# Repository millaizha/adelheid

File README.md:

# 𝕬𝖉𝖊𝖑𝖍𝖊𝖎𝖉

The Adelheid is a 75% Alice-like keyboard.  
It's a fork of FateNozomi's Arisu files: [Arisu PCB](https://github.com/FateNozomi/arisu-pcb) &amp; [Arisu case](https://github.com/FateNozomi/arisu-case)

This repo is a hand-wired version forked from [floookay's Adelheid](https://github.com/floookay/adelheid) with some changes.

This repository includes files for:

- a layered case &rarr; [README.md](./case/README.md)

## Changes in this fork

Here is a list of things I added in this fork in comparison to the original Adelheid:

- [x] replaced page up with a rotary encoder
- [x] lowered home, end, and page up keys (will change into media keys)
- [x] added win and right control keys
- [x] used pro micro as the controller
- [x] changed thickness of some acrylics

## Layout

A spaced 75% layout on top of the Alice/Arisu-layout.

[Keyboard-Layout-Editor](http://www.keyboard-layout-editor.com/#/gists/3d5f924367b3b31ac1beb2d660264759)

## Firmware

See [firmware](https://github.com/millaizha/adelheid-hand-wire/tree/master/firmware)

## Images

For more images see [images.md](./IMAGES.md).

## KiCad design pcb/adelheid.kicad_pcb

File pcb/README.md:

# 𝕬𝖉𝖊𝖑𝖍𝖊𝖎𝖉 - PCB

**Disclaimer:** This PCB revision uses a pin for backlight support that is not PWM enabled. This causes the LEDs to flicker. Everything else works without a problem.  
You can fix this yourself by following [these instructions](../REVISION-UPGRADE-INSTRUCTIONS.md).

The PCB for the Adelheid was designed using KiCAD on top of the Arisu PCB files.

## Changes compared to the Arisu PCB

- [x] Added a spaced function row
- [x] Added footprint for stepped caps lock key
- [x] Changed the micro USB port to a tht mini USB port
- [x] Added single color underglow and key lighting *(underglow on it's own works fine. Both combined have **not been tested yet**)*

## FateNozomi's Arisu description

>アリス PCB designed using KiCad. The layout is inspired by Lyn's EM7 and TGR Alice with some modification of my own.
>
> Key differences:
>
> - I removed the extra [B] key on the right half and shifted the [NM,.?] row > to the left by 0.25U.
> - Shifted the 3 keys to the right and added arrow keys.
> - Tweaked the bottom so that the 1.5U keys doesn't protrude out a little.
>
> Shifting the [NM,.?] row to the left by 0.25U required quite some work on the arrangement of keys for the right half.  
> As a result, this does not give the same typing experience as Lyn's EM7 and TGR Alice.
> Lyn's EM7 and TGR Alice uses the home row as the center point to vertically align both halves while I used the number row instead.  
> Due to the nature of staggered keyboards, aligning using the number row resulted in the home row not being aligned.

The Adelheid inherits these changes from the Arisu.

## KiCAD libraries in use

- [ai03/MX_Only](https://github.com/ai03-2725/MX_Alps_Hybrid/tree/master/MX_Only.pretty) for MX switch footprints (local copy in `./lib/`)
- [Keebio-Parts](https://github.com/keebio/Keebio-Parts.pretty) for mini USB port footprint

## Parts list

### SMD

All SMD parts are listed in the [BOM](./adelheid.gerber/adelheid.csv) with their corresponding value, label and LCSC number.  
If you opt in for LED backlighting/underglow please make sure to use the correct resistor size for your LEDs in order for your PCB to function correctly. See [here](#backlighting) for led resistor estimations.

### THT

- 82x MX switches
- 1x through-hole mini USB 2.0 port (MX-54819-0519)
- (optional) 82x 3mm single color LEDs

## Backlighting

To calculate what resistors you'll need you can use my [backlight calculator spreadsheet](./backlight.ods) to calculate the estimated total power draw. Enter your LED specifications and either enter the desired current per LED or enter the resistor size which you are planning on using. The spreadsheet should calculate the total power draw and compare it to the allowed power draw of USB 2.0 (500 mA). *I'm no electrical engineer so please be cautious.*

<!--  -->

## **Disclaimer**

Use these files at your own risk.  
*Note:* Lighting features have not been entirely tested yet! Please be cautious.

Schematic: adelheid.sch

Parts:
C1, C2: 22pF; C_0805_HandSoldering
C3: 10uF; C_0805_HandSoldering
C4: 1uF (±10%); C_0805_HandSoldering
C5: 1uF; C_0805_HandSoldering
C6, C7, C8, C9: 0.1uF; C_0805_HandSoldering
H1, H2, H3, H4, H5, H6, H7, H8: MountingHole; MountingHole_2.2mm_M2_Pad
J1: USB_B_Mini; USB-Mini-B_2leg
J2: MISO; Pin_Header_Straight_1x01_Pitch2.54mm
J3, J12: VCC; Pin_Header_Straight_1x01_Pitch2.54mm
J4: SCK; Pin_Header_Straight_1x01_Pitch2.54mm
J5: MOSI; Pin_Header_Straight_1x01_Pitch2.54mm
J6: RES; Pin_Header_Straight_1x01_Pitch2.54mm
J7, J15: GND; Pin_Header_Straight_1x01_Pitch2.54mm
J8: PF4; Pin_Header_Straight_1x01_Pitch2.54mm
J9: PF5; Pin_Header_Straight_1x01_Pitch2.54mm
J13: D+; Pin_Header_Straight_1x01_Pitch2.54mm
J14: D-; Pin_Header_Straight_1x01_Pitch2.54mm
Q1: 2N7002; SOT-23
R1, R2: 22; R_0805_2012Metric_Pad1.15x1.40mm_HandSolder
R3, R4: 10K; R_0805_2012Metric_Pad1.15x1.40mm_HandSolder
R5: 1.5K; R_0805_2012Metric_Pad1.15x1.40mm_HandSolder
SWR1: SW_Push; SW_SPST_TL3342
U1: USBLC6-2SC6; SOT-23-6_Handsoldering
U2: ATmega32U4-AU; TQFP-44_10x10mm_Pitch0.8mm
Y1: Crystal_GND24; Crystal_SMD_SeikoEpson_FA238-4pin_3.2x2.5mm_HandSoldering

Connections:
/MISO: J2.1, U2.11 (PB3); also elsewhere on the board
/MOSI: J5.1, U2.10 (PB2)
/PF4: J8.1, U2.39 (PF4)
/PF5: J9.1, U2.38 (PF5)
/SCK: J4.1, U2.9 (PB1); also elsewhere on the board
/col0: U2.41 (PF0); also elsewhere on the board
/col1: U2.40 (PF1); also elsewhere on the board
/col2: U2.1 (PE6); also elsewhere on the board
/col3: U2.32 (PC7); also elsewhere on the board
/col4: U2.31 (PC6); also elsewhere on the board
/col5: U2.30 (PB6); also elsewhere on the board
/col6: U2.25 (PD4); also elsewhere on the board
/col8: U2.8 (PB0); also elsewhere on the board
/col9: U2.12 (PB7); also elsewhere on the board
/col10: U2.29 (PB5); also elsewhere on the board
/col11: U2.28 (PB4); also elsewhere on the board
/col12: U2.27 (PD7); also elsewhere on the board
/col13: U2.26 (PD6); also elsewhere on the board
/ledGND: Q1.3; also elsewhere on the board
/row0: U2.18 (PD0); also elsewhere on the board
/row1: U2.19 (PD1); also elsewhere on the board
/row2: U2.20 (PD2); also elsewhere on the board
/row3: U2.21 (PD3); also elsewhere on the board
/row4: U2.22 (PD5); also elsewhere on the board
/row5: U2.36 (PF7); also elsewhere on the board
/~RES~: J6.1, R3.2, SWR1.2, U2.13 (~RESET)
D+: R1.1, U2.4 (D+)
D-: R2.1, U2.3 (D-)
GND: C1.1, C2.2, C3.2, C4.2, C5.2, C6.2, C7.2, C8.2, C9.2, J1.5 (GND), J1.6 (Shield), J7.1, J15.1, Q1.2, R4.2, SWR1.1, U1.2 (GND), U2.5 (UGND), U2.15 (GND), U2.23 (GND), U2.35 (GND), U2.43 (GND), Y1.2, Y1.4
unnamed: C4.1, U2.6 (UCAP)
unnamed: J1.2 (D-), J14.1, R2.2, U1.4 (IO2)
unnamed: J1.3 (D+), J13.1, R1.2, U1.6 (IO1)
unnamed: Q1.1, R5.2
unnamed: R4.1, U2.33 (~HWB~/PE2)
unnamed: R5.1, U2.37 (PF6)
VCC: C3.1, C5.1, C6.1, C7.1, C8.1, C9.1, J1.1 (VBUS), J3.1, J12.1, R3.1, U1.5 (VBUS), U2.2 (UVCC), U2.7 (VBUS), U2.14 (VCC), U2.24 (AVCC), U2.34 (VCC), U2.44 (AVCC); also elsewhere on the board
XTAL1: C1.2, U2.17 (XTAL1), Y1.1
XTAL2: C2.1, U2.16 (XTAL2), Y1.3

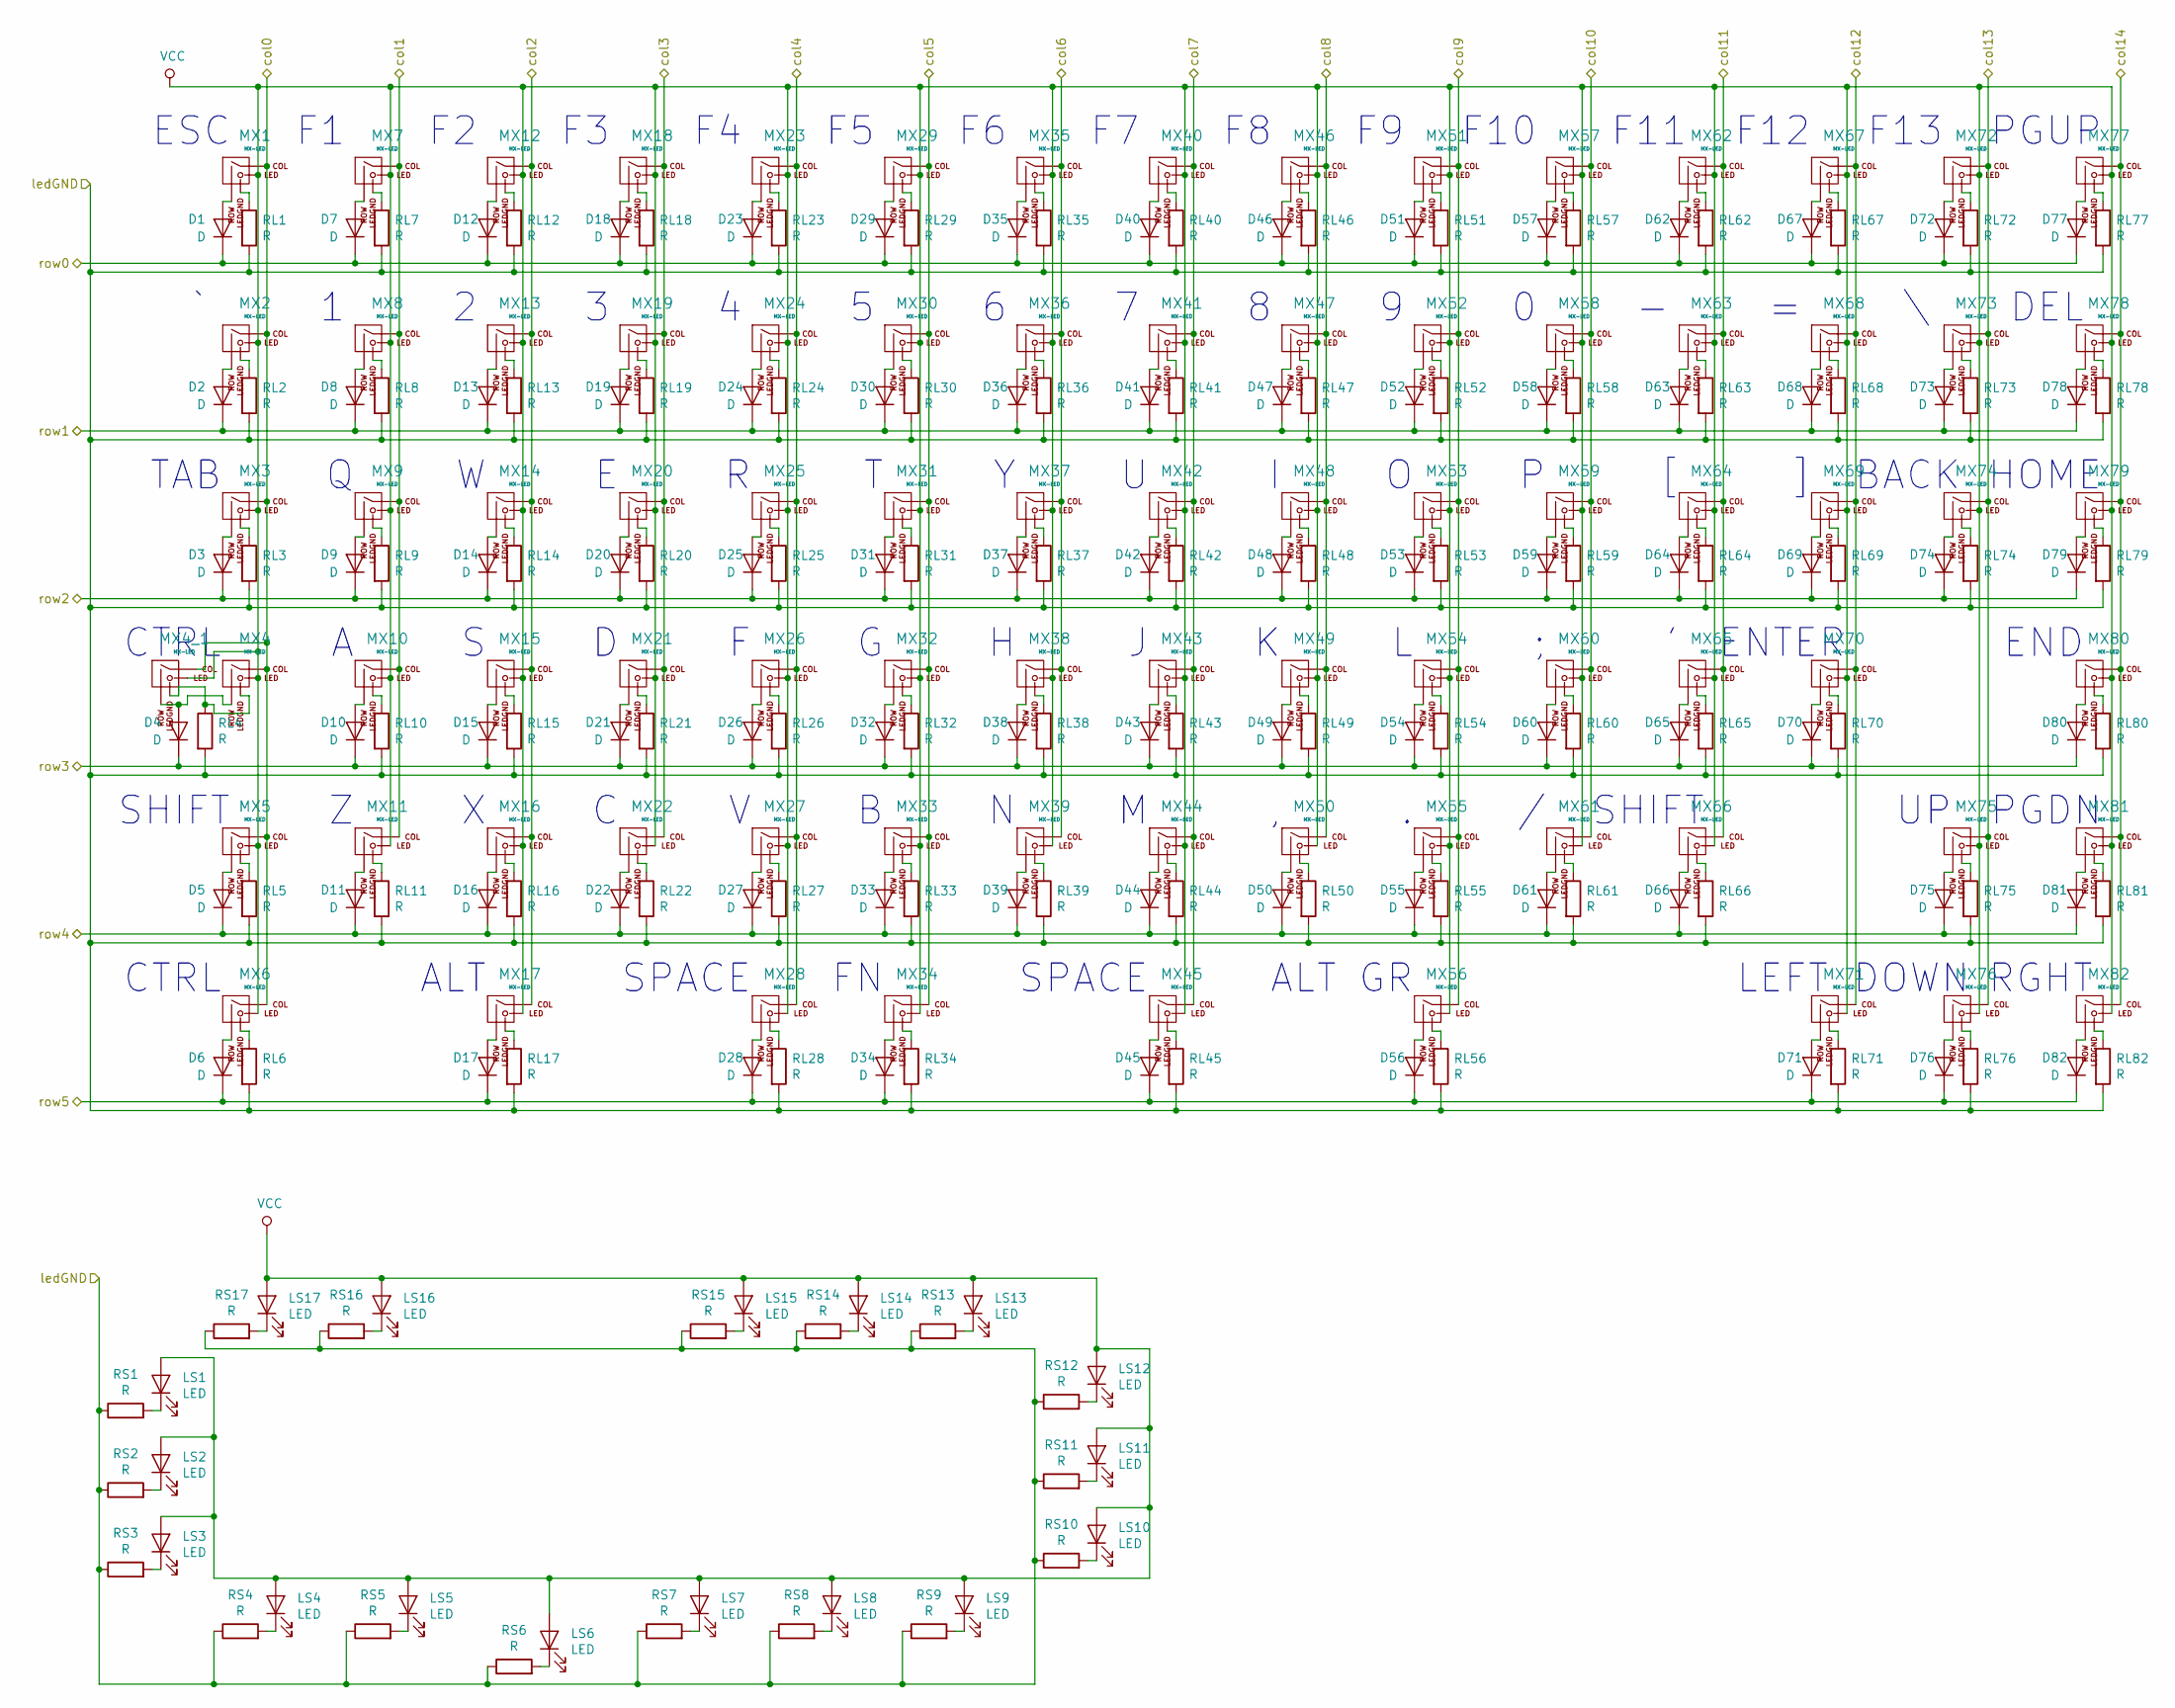
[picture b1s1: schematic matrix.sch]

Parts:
D1, D2, D3, D4, D5, D6, D7, D8, D9, D10, D11, D12, D13, D14, D15, D16, D17, D18, D19, D20, D21, D22, D23, D24, D25, D26, D27, D28, D29, D30, D31, D32, D33, D34, D35, D36, D37, D38, D39, D40, D41, D42, D43, D44, D45, D46, D47, D48, D49, D50, D51, D52, D53, D54, D55, D56, D57, D58, D59, D60, D61, D62, D63, D64, D65, D66, D67, D68, D69, D70, D71, D72, D73, D74, D75, D76, D77, D78, D79, D80, D81, D82: D; D_SOD-123
LS1, LS2, LS3, LS4, LS5, LS6, LS7, LS8, LS9, LS10, LS11, LS12, LS13, LS14, LS15, LS16, LS17: LED; LED_0805_2012Metric_Pad1.15x1.40mm_HandSolder
MX1, MX2, MX7, MX8, MX9, MX10, MX11, MX12, MX13, MX14, MX15, MX16, MX18, MX19, MX20, MX21, MX22, MX23, MX24, MX25, MX26, MX27, MX29, MX30, MX31, MX32, MX33, MX34, MX35, MX36, MX37, MX38, MX39, MX40, MX41, MX42, MX43, MX44, MX46, MX47, MX48, MX49, MX50, MX51, MX52, MX53, MX54, MX55, MX57, MX58, MX59, MX60, MX61, MX62, MX63, MX64, MX65, MX67, MX68, MX69, MX71, MX72, MX73, MX75, MX76, MX77, MX78, MX79, MX80, MX81, MX82: MX-LED; MXOnly-1U
MX3, MX6, MX17, MX56, MX74: MX-LED; MXOnly-1.5U
MX4, MX66: MX-LED; MXOnly-1.75U
MX4_1: MX-LED; MXOnly-1.75U-FLIPPED
MX5: MX-LED; MXOnly-2.25U
MX28: MX-LED; MXOnly-2U-ReversedStabilizers
MX45: MX-LED; MXOnly-2.75U-ReversedStabilizers
MX70: MX-LED; MXOnly-2.25U-ReversedStabilizers
RL1, RL2, RL3, RL4, RL5, RL6, RL7, RL8, RL9, RL10, RL11, RL12, RL13, RL14, RL15, RL16, RL17, RL18, RL19, RL20, RL21, RL22, RL23, RL24, RL25, RL26, RL27, RL28, RL29, RL30, RL31, RL32, RL33, RL34, RL35, RL36, RL37, RL38, RL39, RL40, RL41, RL42, RL43, RL44, RL45, RL46, RL47, RL48, RL49, RL50, RL51, RL52, RL53, RL54, RL55, RL56, RL57, RL58, RL59, RL60, RL61, RL62, RL63, RL64, RL65, RL66, RL67, RL68, RL69, RL70, RL71, RL72, RL73, RL74, RL75, RL76, RL77, RL78, RL79, RL80, RL81, RL82: R; R_0805_2012Metric_Pad1.15x1.40mm_HandSolder
RS1, RS2, RS3, RS4, RS5, RS6, RS7, RS8, RS9, RS10, RS11, RS12, RS13, RS14, RS15, RS16, RS17: R; R_0805_2012Metric_Pad1.15x1.40mm_HandSolder

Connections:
/MISO: MX77.1 (COL), MX78.1 (COL), MX79.1 (COL), MX80.1 (COL), MX81.1 (COL), MX82.1 (COL); also elsewhere on the board
/SCK: MX40.1 (COL), MX41.1 (COL), MX42.1 (COL), MX43.1 (COL), MX44.1 (COL), MX45.1 (COL); also elsewhere on the board
/col0: MX1.1 (COL), MX2.1 (COL), MX3.1 (COL), MX4.1 (COL), MX4_1.1 (COL), MX5.1 (COL), MX6.1 (COL); also elsewhere on the board
/col1: MX7.1 (COL), MX8.1 (COL), MX9.1 (COL), MX10.1 (COL), MX11.1 (COL); also elsewhere on the board
/col2: MX12.1 (COL), MX13.1 (COL), MX14.1 (COL), MX15.1 (COL), MX16.1 (COL), MX17.1 (COL); also elsewhere on the board
/col3: MX18.1 (COL), MX19.1 (COL), MX20.1 (COL), MX21.1 (COL), MX22.1 (COL); also elsewhere on the board
/col4: MX23.1 (COL), MX24.1 (COL), MX25.1 (COL), MX26.1 (COL), MX27.1 (COL), MX28.1 (COL); also elsewhere on the board
/col5: MX29.1 (COL), MX30.1 (COL), MX31.1 (COL), MX32.1 (COL), MX33.1 (COL), MX34.1 (COL); also elsewhere on the board
/col6: MX35.1 (COL), MX36.1 (COL), MX37.1 (COL), MX38.1 (COL), MX39.1 (COL); also elsewhere on the board
/col8: MX46.1 (COL), MX47.1 (COL), MX48.1 (COL), MX49.1 (COL), MX50.1 (COL); also elsewhere on the board
/col9: MX51.1 (COL), MX52.1 (COL), MX53.1 (COL), MX54.1 (COL), MX55.1 (COL), MX56.1 (COL); also elsewhere on the board
/col10: MX57.1 (COL), MX58.1 (COL), MX59.1 (COL), MX60.1 (COL), MX61.1 (COL); also elsewhere on the board
/col11: MX62.1 (COL), MX63.1 (COL), MX64.1 (COL), MX65.1 (COL), MX66.1 (COL); also elsewhere on the board
/col12: MX67.1 (COL), MX68.1 (COL), MX69.1 (COL), MX70.1 (COL), MX71.1 (COL); also elsewhere on the board
/col13: MX72.1 (COL), MX73.1 (COL), MX74.1 (COL), MX75.1 (COL), MX76.1 (COL); also elsewhere on the board
/ledGND: RL1.2, RL2.2, RL3.2, RL4.2, RL5.2, RL6.2, RL7.2, RL8.2, RL9.2, RL10.2, RL11.2, RL12.2, RL13.2, RL14.2, RL15.2, RL16.2, RL17.2, RL18.2, RL19.2, RL20.2, RL21.2, RL22.2, RL23.2, RL24.2, RL25.2, RL26.2, RL27.2, RL28.2, RL29.2, RL30.2, RL31.2, RL32.2, RL33.2, RL34.2, RL35.2, RL36.2, RL37.2, RL38.2, RL39.2, RL40.2, RL41.2, RL42.2, RL43.2, RL44.2, RL45.2, RL46.2, RL47.2, RL48.2, RL49.2, RL50.2, RL51.2, RL52.2, RL53.2, RL54.2, RL55.2, RL56.2, RL57.2, RL58.2, RL59.2, RL60.2, RL61.2, RL62.2, RL63.2, RL64.2, RL65.2, RL66.2, RL67.2, RL68.2, RL69.2, RL70.2, RL71.2, RL72.2, RL73.2, RL74.2, RL75.2, RL76.2, RL77.2, RL78.2, RL79.2, RL80.2, RL81.2, RL82.2, RS1.1, RS2.1, RS3.1, RS4.1, RS5.1, RS6.1, RS7.1, RS8.1, RS9.1, RS10.1, RS11.1, RS12.1, RS13.1, RS14.1, RS15.1, RS16.1, RS17.1; also elsewhere on the board
/row0: D1.1 (K), D7.1 (K), D12.1 (K), D18.1 (K), D23.1 (K), D29.1 (K), D35.1 (K), D40.1 (K), D46.1 (K), D51.1 (K), D57.1 (K), D62.1 (K), D67.1 (K), D72.1 (K), D77.1 (K); also elsewhere on the board
/row1: D2.1 (K), D8.1 (K), D13.1 (K), D19.1 (K), D24.1 (K), D30.1 (K), D36.1 (K), D41.1 (K), D47.1 (K), D52.1 (K), D58.1 (K), D63.1 (K), D68.1 (K), D73.1 (K), D78.1 (K); also elsewhere on the board
/row2: D3.1 (K), D9.1 (K), D14.1 (K), D20.1 (K), D25.1 (K), D31.1 (K), D37.1 (K), D42.1 (K), D48.1 (K), D53.1 (K), D59.1 (K), D64.1 (K), D69.1 (K), D74.1 (K), D79.1 (K); also elsewhere on the board
/row3: D4.1 (K), D10.1 (K), D15.1 (K), D21.1 (K), D26.1 (K), D32.1 (K), D38.1 (K), D43.1 (K), D49.1 (K), D54.1 (K), D60.1 (K), D65.1 (K), D70.1 (K), D80.1 (K); also elsewhere on the board
/row4: D5.1 (K), D11.1 (K), D16.1 (K), D22.1 (K), D27.1 (K), D33.1 (K), D39.1 (K), D44.1 (K), D50.1 (K), D55.1 (K), D61.1 (K), D66.1 (K), D75.1 (K), D81.1 (K); also elsewhere on the board
/row5: D6.1 (K), D17.1 (K), D28.1 (K), D34.1 (K), D45.1 (K), D56.1 (K), D71.1 (K), D76.1 (K), D82.1 (K); also elsewhere on the board
unnamed: D1.2 (A), MX1.2 (ROW)
unnamed: D2.2 (A), MX2.2 (ROW)
unnamed: D3.2 (A), MX3.2 (ROW)
unnamed: D4.2 (A), MX4.2 (ROW), MX4_1.2 (ROW)
unnamed: D5.2 (A), MX5.2 (ROW)
unnamed: D6.2 (A), MX6.2 (ROW)
unnamed: D7.2 (A), MX7.2 (ROW)
unnamed: D8.2 (A), MX8.2 (ROW)
unnamed: D9.2 (A), MX9.2 (ROW)
unnamed: D10.2 (A), MX10.2 (ROW)
unnamed: D11.2 (A), MX11.2 (ROW)
unnamed: D12.2 (A), MX12.2 (ROW)
unnamed: D13.2 (A), MX13.2 (ROW)
unnamed: D14.2 (A), MX14.2 (ROW)
unnamed: D15.2 (A), MX15.2 (ROW)
unnamed: D16.2 (A), MX16.2 (ROW)
unnamed: D17.2 (A), MX17.2 (ROW)
unnamed: D18.2 (A), MX18.2 (ROW)
unnamed: D19.2 (A), MX19.2 (ROW)
unnamed: D20.2 (A), MX20.2 (ROW)
unnamed: D21.2 (A), MX21.2 (ROW)
unnamed: D22.2 (A), MX22.2 (ROW)
unnamed: D23.2 (A), MX23.2 (ROW)
unnamed: D24.2 (A), MX24.2 (ROW)
unnamed: D25.2 (A), MX25.2 (ROW)
unnamed: D26.2 (A), MX26.2 (ROW)
unnamed: D27.2 (A), MX27.2 (ROW)
unnamed: D28.2 (A), MX28.2 (ROW)
unnamed: D29.2 (A), MX29.2 (ROW)
unnamed: D30.2 (A), MX30.2 (ROW)
unnamed: D31.2 (A), MX31.2 (ROW)
unnamed: D32.2 (A), MX32.2 (ROW)
unnamed: D33.2 (A), MX33.2 (ROW)
unnamed: D34.2 (A), MX34.2 (ROW)
unnamed: D35.2 (A), MX35.2 (ROW)
unnamed: D36.2 (A), MX36.2 (ROW)
unnamed: D37.2 (A), MX37.2 (ROW)
unnamed: D38.2 (A), MX38.2 (ROW)
unnamed: D39.2 (A), MX39.2 (ROW)
unnamed: D40.2 (A), MX40.2 (ROW)
unnamed: D41.2 (A), MX41.2 (ROW)
unnamed: D42.2 (A), MX42.2 (ROW)
unnamed: D43.2 (A), MX43.2 (ROW)
unnamed: D44.2 (A), MX44.2 (ROW)
unnamed: D45.2 (A), MX45.2 (ROW)
unnamed: D46.2 (A), MX46.2 (ROW)
unnamed: D47.2 (A), MX47.2 (ROW)
unnamed: D48.2 (A), MX48.2 (ROW)
unnamed: D49.2 (A), MX49.2 (ROW)
unnamed: D50.2 (A), MX50.2 (ROW)
unnamed: D51.2 (A), MX51.2 (ROW)
unnamed: D52.2 (A), MX52.2 (ROW)
unnamed: D53.2 (A), MX53.2 (ROW)
unnamed: D54.2 (A), MX54.2 (ROW)
unnamed: D55.2 (A), MX55.2 (ROW)
unnamed: D56.2 (A), MX56.2 (ROW)
unnamed: D57.2 (A), MX57.2 (ROW)
unnamed: D58.2 (A), MX58.2 (ROW)
unnamed: D59.2 (A), MX59.2 (ROW)
unnamed: D60.2 (A), MX60.2 (ROW)
unnamed: D61.2 (A), MX61.2 (ROW)
unnamed: D62.2 (A), MX62.2 (ROW)
unnamed: D63.2 (A), MX63.2 (ROW)
unnamed: D64.2 (A), MX64.2 (ROW)
unnamed: D65.2 (A), MX65.2 (ROW)
unnamed: D66.2 (A), MX66.2 (ROW)
unnamed: D67.2 (A), MX67.2 (ROW)
unnamed: D68.2 (A), MX68.2 (ROW)
unnamed: D69.2 (A), MX69.2 (ROW)
unnamed: D70.2 (A), MX70.2 (ROW)
unnamed: D71.2 (A), MX71.2 (ROW)
unnamed: D72.2 (A), MX72.2 (ROW)
unnamed: D73.2 (A), MX73.2 (ROW)
unnamed: D74.2 (A), MX74.2 (ROW)
unnamed: D75.2 (A), MX75.2 (ROW)
unnamed: D76.2 (A), MX76.2 (ROW)
unnamed: D77.2 (A), MX77.2 (ROW)
unnamed: D78.2 (A), MX78.2 (ROW)
unnamed: D79.2 (A), MX79.2 (ROW)
unnamed: D80.2 (A), MX80.2 (ROW)
unnamed: D81.2 (A), MX81.2 (ROW)
unnamed: D82.2 (A), MX82.2 (ROW)
unnamed: LS1.1 (K), RS1.2
unnamed: LS2.1 (K), RS2.2
unnamed: LS3.1 (K), RS3.2
unnamed: LS4.1 (K), RS4.2
unnamed: LS5.1 (K), RS5.2
unnamed: LS6.1 (K), RS6.2
unnamed: LS7.1 (K), RS7.2
unnamed: LS8.1 (K), RS8.2
unnamed: LS9.1 (K), RS9.2
unnamed: LS10.1 (K), RS10.2
unnamed: LS11.1 (K), RS11.2
unnamed: LS12.1 (K), RS12.2
unnamed: LS13.1 (K), RS13.2
unnamed: LS14.1 (K), RS14.2
unnamed: LS15.1 (K), RS15.2
unnamed: LS16.1 (K), RS16.2
unnamed: LS17.1 (K), RS17.2
unnamed: MX1.4 (LEDGND), RL1.1
unnamed: MX2.4 (LEDGND), RL2.1
unnamed: MX3.4 (LEDGND), RL3.1
unnamed: MX4.4 (LEDGND), MX4_1.4 (LEDGND), RL4.1
unnamed: MX5.4 (LEDGND), RL5.1
unnamed: MX6.4 (LEDGND), RL6.1
unnamed: MX7.4 (LEDGND), RL7.1
unnamed: MX8.4 (LEDGND), RL8.1
unnamed: MX9.4 (LEDGND), RL9.1
unnamed: MX10.4 (LEDGND), RL10.1
unnamed: MX11.4 (LEDGND), RL11.1
unnamed: MX12.4 (LEDGND), RL12.1
unnamed: MX13.4 (LEDGND), RL13.1
unnamed: MX14.4 (LEDGND), RL14.1
unnamed: MX15.4 (LEDGND), RL15.1
unnamed: MX16.4 (LEDGND), RL16.1
unnamed: MX17.4 (LEDGND), RL17.1
unnamed: MX18.4 (LEDGND), RL18.1
unnamed: MX19.4 (LEDGND), RL19.1
unnamed: MX20.4 (LEDGND), RL20.1
unnamed: MX21.4 (LEDGND), RL21.1
unnamed: MX22.4 (LEDGND), RL22.1
unnamed: MX23.4 (LEDGND), RL23.1
unnamed: MX24.4 (LEDGND), RL24.1
unnamed: MX25.4 (LEDGND), RL25.1
unnamed: MX26.4 (LEDGND), RL26.1
unnamed: MX27.4 (LEDGND), RL27.1
unnamed: MX28.4 (LEDGND), RL28.1
unnamed: MX29.4 (LEDGND), RL29.1
unnamed: MX30.4 (LEDGND), RL30.1
unnamed: MX31.4 (LEDGND), RL31.1
unnamed: MX32.4 (LEDGND), RL32.1
unnamed: MX33.4 (LEDGND), RL33.1
unnamed: MX34.4 (LEDGND), RL34.1
unnamed: MX35.4 (LEDGND), RL35.1
unnamed: MX36.4 (LEDGND), RL36.1
unnamed: MX37.4 (LEDGND), RL37.1
unnamed: MX38.4 (LEDGND), RL38.1
unnamed: MX39.4 (LEDGND), RL39.1
unnamed: MX40.4 (LEDGND), RL40.1
unnamed: MX41.4 (LEDGND), RL41.1
unnamed: MX42.4 (LEDGND), RL42.1
unnamed: MX43.4 (LEDGND), RL43.1
unnamed: MX44.4 (LEDGND), RL44.1
unnamed: MX45.4 (LEDGND), RL45.1
unnamed: MX46.4 (LEDGND), RL46.1
unnamed: MX47.4 (LEDGND), RL47.1
unnamed: MX48.4 (LEDGND), RL48.1
unnamed: MX49.4 (LEDGND), RL49.1
unnamed: MX50.4 (LEDGND), RL50.1
unnamed: MX51.4 (LEDGND), RL51.1
unnamed: MX52.4 (LEDGND), RL52.1
unnamed: MX53.4 (LEDGND), RL53.1
unnamed: MX54.4 (LEDGND), RL54.1
unnamed: MX55.4 (LEDGND), RL55.1
unnamed: MX56.4 (LEDGND), RL56.1
unnamed: MX57.4 (LEDGND), RL57.1
unnamed: MX58.4 (LEDGND), RL58.1
unnamed: MX59.4 (LEDGND), RL59.1
unnamed: MX60.4 (LEDGND), RL60.1
unnamed: MX61.4 (LEDGND), RL61.1
unnamed: MX62.4 (LEDGND), RL62.1
unnamed: MX63.4 (LEDGND), RL63.1
unnamed: MX64.4 (LEDGND), RL64.1
unnamed: MX65.4 (LEDGND), RL65.1
unnamed: MX66.4 (LEDGND), RL66.1
unnamed: MX67.4 (LEDGND), RL67.1
unnamed: MX68.4 (LEDGND), RL68.1
unnamed: MX69.4 (LEDGND), RL69.1
unnamed: MX70.4 (LEDGND), RL70.1
unnamed: MX71.4 (LEDGND), RL71.1
unnamed: MX72.4 (LEDGND), RL72.1
unnamed: MX73.4 (LEDGND), RL73.1
unnamed: MX74.4 (LEDGND), RL74.1
unnamed: MX75.4 (LEDGND), RL75.1
unnamed: MX76.4 (LEDGND), RL76.1
unnamed: MX77.4 (LEDGND), RL77.1
unnamed: MX78.4 (LEDGND), RL78.1
unnamed: MX79.4 (LEDGND), RL79.1
unnamed: MX80.4 (LEDGND), RL80.1
unnamed: MX81.4 (LEDGND), RL81.1
unnamed: MX82.4 (LEDGND), RL82.1
VCC: LS1.2 (A), LS2.2 (A), LS3.2 (A), LS4.2 (A), LS5.2 (A), LS6.2 (A), LS7.2 (A), LS8.2 (A), LS9.2 (A), LS10.2 (A), LS11.2 (A), LS12.2 (A), LS13.2 (A), LS14.2 (A), LS15.2 (A), LS16.2 (A), LS17.2 (A), MX1.3 (LED), MX2.3 (LED), MX3.3 (LED), MX4.3 (LED), MX4_1.3 (LED), MX5.3 (LED), MX6.3 (LED), MX7.3 (LED), MX8.3 (LED), MX9.3 (LED), MX10.3 (LED), MX11.3 (LED), MX12.3 (LED), MX13.3 (LED), MX14.3 (LED), MX15.3 (LED), MX16.3 (LED), MX17.3 (LED), MX18.3 (LED), MX19.3 (LED), MX20.3 (LED), MX21.3 (LED), MX22.3 (LED), MX23.3 (LED), MX24.3 (LED), MX25.3 (LED), MX26.3 (LED), MX27.3 (LED), MX28.3 (LED), MX29.3 (LED), MX30.3 (LED), MX31.3 (LED), MX32.3 (LED), MX33.3 (LED), MX34.3 (LED), MX35.3 (LED), MX36.3 (LED), MX37.3 (LED), MX38.3 (LED), MX39.3 (LED), MX40.3 (LED), MX41.3 (LED), MX42.3 (LED), MX43.3 (LED), MX44.3 (LED), MX45.3 (LED), MX46.3 (LED), MX47.3 (LED), MX48.3 (LED), MX49.3 (LED), MX50.3 (LED), MX51.3 (LED), MX52.3 (LED), MX53.3 (LED), MX54.3 (LED), MX55.3 (LED), MX56.3 (LED), MX57.3 (LED), MX58.3 (LED), MX59.3 (LED), MX60.3 (LED), MX61.3 (LED), MX62.3 (LED), MX63.3 (LED), MX64.3 (LED), MX65.3 (LED), MX66.3 (LED), MX67.3 (LED), MX68.3 (LED), MX69.3 (LED), MX70.3 (LED), MX71.3 (LED), MX72.3 (LED), MX73.3 (LED), MX74.3 (LED), MX75.3 (LED), MX76.3 (LED), MX77.3 (LED), MX78.3 (LED), MX79.3 (LED), MX80.3 (LED), MX81.3 (LED), MX82.3 (LED); also elsewhere on the board

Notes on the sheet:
ESC
F10
F11
F12
F13
PGUP
DEL
HOME
END
PGDN
RGHT
DOWN
LEFT
TAB
BACK
CTRL
ENTER
SHIFT
ALT
SPACE
ALT GR

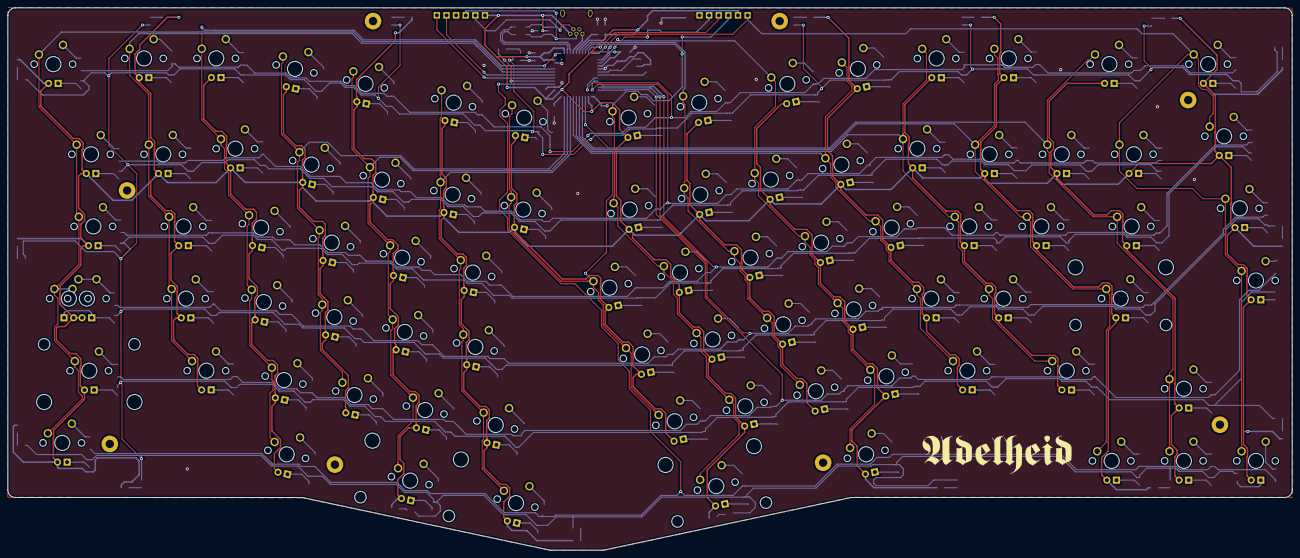
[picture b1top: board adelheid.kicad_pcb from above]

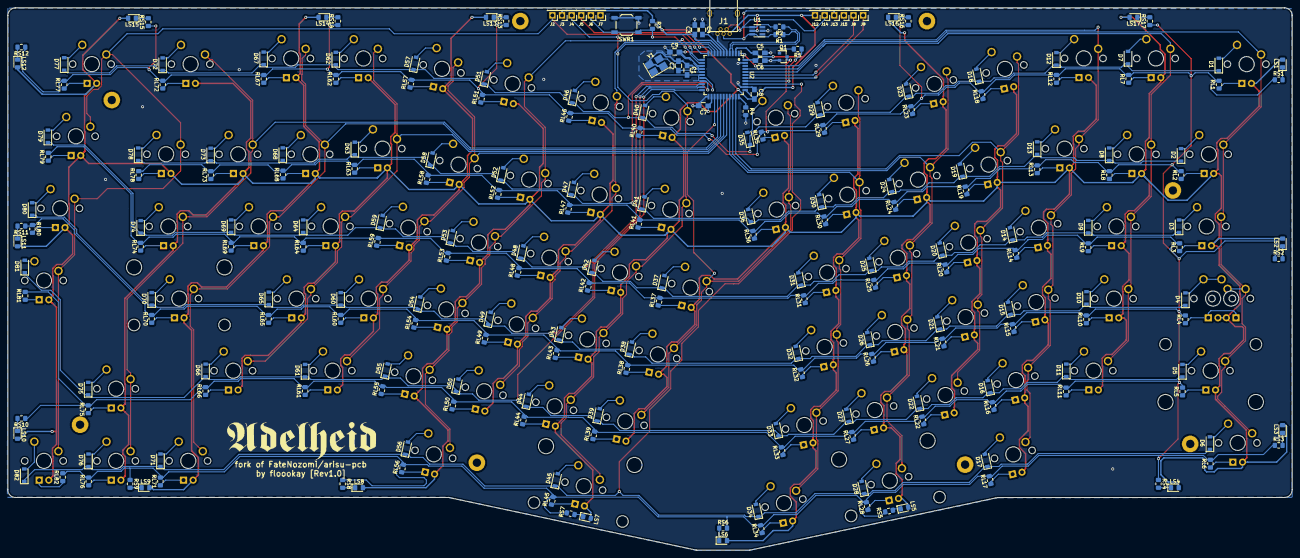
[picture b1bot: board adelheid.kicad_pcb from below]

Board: 2 copper layers, 339.1 x 143.2 mm, 323 parts (231 on the bottom side), 219 nets.

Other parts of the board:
 G2: LOGO; adelheid-logo
G1: LOGO; adelheid-logo

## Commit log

2020-04-16 added gerber files
2020-04-16 updated case files
2020-04-20 updated readmes
2020-04-27 added images of PCB and acrylic case layers
2020-04-27 updated pcb labels to be more consistent [v1.0.1]
2020-05-18 added footprints
2020-05-18 added column and row routing
2020-05-18 added matrix routing
2020-05-18 finished pcb v2
2020-05-18 added mx-library by ai03
2020-05-18 restructured folder structure
2020-05-20 updated readme + preparation for merge
2020-05-20 moved images to seperate repo & updated readmes
2020-05-25 restructured case files, updated readmes
2020-05-25 updated pcb readme
2020-05-26 added clarification
2020-05-27 made usb port cutout slightly larger
2020-05-28 fixed revision number [Rev1.0]
2020-05-28 made usb port cutout larger in 600x600mm sheets
2020-05-28 updated image links
    - commented out redundant images
    - added image carousel
2020-05-29 fixed typo
    well not a typo but "caroussel" doesn't fit
2020-06-01 altered hipro function row cutouts slightly
    these were slightly larger on the left half and have been resized so
    the cutouts should be more symmetrical now
2020-06-11 made pcb file compatible with stable KiCAD release
    compatible with KiCAD >5.1.6
    Previously pcbnew was only working with a testing build of KiCAD.
2020-07-11 switched backlight pin [Rev2.0]
    swapped col4 and led pin.
    Backlight is now on pin 31 (C6).
    In Rev1.0 the backlight started flickering because the MCU couldn't
    handle the load of the LEDs on pin 37. This should fix the issue.
    Thank you u/SryImBadAtNaming for finding out and notifying me!
2020-07-11 added instructions on how to upgrade to Rev2.0
2020-07-12 fixed typo
2020-07-14 adjusted canvas size
2020-07-14 added assembly parts list and standoffs to flat wr
2020-07-14 fixed error in parts list
2020-07-15 tested backlight support
    - tested backlight support for Rev2.0
    (200mA power draw with 99 LEDs at 1kΩ each
    - removed backlight support disclaimers
    - added tentative backlight picture
2020-07-17 added QMK firmware link
2020-09-14 removed scale
2021-03-20 added proto files for plate foam
2021-12-04 Add case files
2021-12-04 Add layout
